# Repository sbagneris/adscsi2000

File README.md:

# ICD AdSCSI 2000 (Advantage 2000) - hardware preservation

The ICD AdSCSI 2000 (silkscreen "ADVANTAGE 2000", 1990) is a Zorro II SCSI controller for the Amiga 2000. Its
three GAL16V8 chips are read-protected and, like many programmable logic parts of that era, are reaching the end
of their data retention. This repository preserves the card: what each GAL does, the complete circuit, and the
measurements behind both, so the card can be repaired, understood and rebuilt.

## What is here

| Path | Contents |
|---|---|
| `docs/hardware.md` | How the card works: Autoconfig, address map, registers, what each GAL does, jumpers, connectors |
| `gals/u3`, `gals/u4`, `gals/u5` | Per-GAL characterisation data and the recovered logic (see below) |
| `gals/uN/uN_named.pld` / `.jed` | GALasm source with board signal names, and the JEDEC file to program a replacement |
| `docs/gal-replacements.md` | Replacement GALs programmed from these files, checked against the originals on the bench and in a real Amiga |
| `schematic/kicad/` | KiCad 10 project: root sheet + 6 sheets, project symbol and footprint libraries, `adscsi2000.pdf`, and the clone PCB (`adscsi2000.kicad_pcb`) |
| `schematic/kicad/fab/` | Ready-to-order clone PCB: gerbers + drill files (`adscsi2000_gerbers.zip`), BOM, previews, `ORDER_NOTES.txt` |
| `schematic/netlist/merged.csv` | The measured netlist: 116 nets, 518 pins |
| `schematic/continuity/` | The raw continuity sweeps the netlist was built from |
| `schematic/tools/` | Photo registration, netlist merging, the netlist-to-KiCad schematic generator and the PCB pipeline |
| `inputs/closeups*/`, `inputs/mycard_*` | Photos of the measured card (both sides, close-up tiles, GAL footprints without sockets) |

## How the GALs were recovered

The originals are secured, so their fuse maps cannot be read. Each chip was characterised in a DuPAL V3
("dupico") board, read-only:

1. A first look classified pins (inputs, driven outputs, tri-stated outputs) and a second read in a different
   input order showed that all three GALs hold state (latches built from output feedback; U4 also uses registers).
2. Each chip's behaviour was mapped exhaustively one input change at a time (and one clock pulse at a time for the
   registered U4): every reachable state and every move from it (`gals/uN/uN_moves*.tsv`), with replays and
   re-clocking to rule out measurement errors.
3. Equations were fitted with espresso and refined until every recorded move (U3 79,824, U4 70,880, U5 12,080)
   replays exactly with outputs allowed to settle in any order (`gals/uN/uN_fit.txt`).
4. GALasm sources were generated and the resulting fuse maps were replayed against the recordings again.

These are **equivalent** equations: they reproduce everything the original can do in circuit, but the secured
originals' exact product terms are unknowable. Combinations the circuit can never reach were don't-cares.

The tools are in the companion repository
[gal-dupico-re](https://github.com/sbagneris/gal-dupico-re).

**Verified on real chips.** ATF16V8B copies programmed from these JEDEC files replay every recorded move of the
originals with no mismatch, and run the card in an Amiga 2000 exactly like the originals: same boots, same quirks,
on both a 68000 and a 68030. See `docs/gal-replacements.md`.

## The clone PCB

A 1:1 through-hole clone of the card, made to validate this work in a real Amiga 2000:

- **Same parts, same places.** Every footprint was fitted to the pin positions measured on the original (scan
  calibrated so all 41 parts land on the original's 0.025" grid), with the outline, mounting holes and finger tab from
  caliper measurements and the Zorro mechanical spec (finger tab 129.26 mm).
- **Same circuit.** The PCB is generated from the measured netlist; KiCad's schematic-parity check is clean.
- **Better ground than the original.** The original has no ground pour; the clone has GND pours on both layers tied
  together by a stitching-via grid every 5 mm, which should help on noisy Zorro buses (68040 accelerators are known to
  trouble the original).
- Two layers, 1.6 mm, signals autorouted (Freerouting) and checked: DRC clean, every documented exception listed in
  `schematic/kicad/drc_accepted.tsv` with its reason.

To order: upload `schematic/kicad/fab/adscsi2000_gerbers.zip` and follow `ORDER_NOTES.txt` (gold fingers with a
bevelled edge). Component values are in the BOM (`adscsi2000_bom.csv`). The three GALs are programmed from
`gals/uN/uN_named.jed` (security fuse off); the boot ROM is not included (see below).

The whole board is reproducible from the scripts in `schematic/tools/`: `pcb_route.sh` (generate + autoroute) then
`pcb_finish.sh` (pours, ground stitching, hand edits replayed, labels, DRC exclusions) and `pcb_fab.sh` (fab outputs).

**Status: not yet built or tested.** The first boards are the test of everything in this repository.

## Status

- GAL logic recovered and named; replacement ATF16V8B chips programmed from the JEDEC files verified on the bench
  (every recorded move of the originals) and in the card (drop-in: same behaviour as the originals).
- Netlist complete and confirmed by continuity on a real card; KiCad schematic generated from it: the exported
  netlist matches the measurements on all 116 nets, ERC clean.
- Clone PCB designed and ready to order (above); next: build and test it, then a compact SMD version.

## Not included

The boot ROM image and ICD's software are copyrighted by ICD Inc. and are not distributed here. Neither are the
third-party reference photos used early on.

## Licences

- Hardware design (`schematic/kicad/`: schematic, PCB, footprints and fabrication files): CERN-OHL-S-2.0
- Software (`schematic/tools/`, scripts): BSD-3-Clause
- Documentation, measurement data, recovered GAL equations and JEDEC files, photos: CC BY-SA 4.0

See `LICENSE.md` and `LICENSES/`. "ICD", "AdSCSI" and "Advantage 2000" are names of their respective owners; this
is an independent preservation project.

## Credits

Measurements, photos and bench work: Stephane Bagneris. Analysis and tooling written with Claude (Anthropic).
DuPAL by the [DuPAL-PAL-DUmper](https://github.com/DuPAL-PAL-DUmper) project. Zorro II pinout from the Amiga
Hardware Reference Manual; 5380 pinout from the NCR 5380 SCSI Interface Chip Design Manual.

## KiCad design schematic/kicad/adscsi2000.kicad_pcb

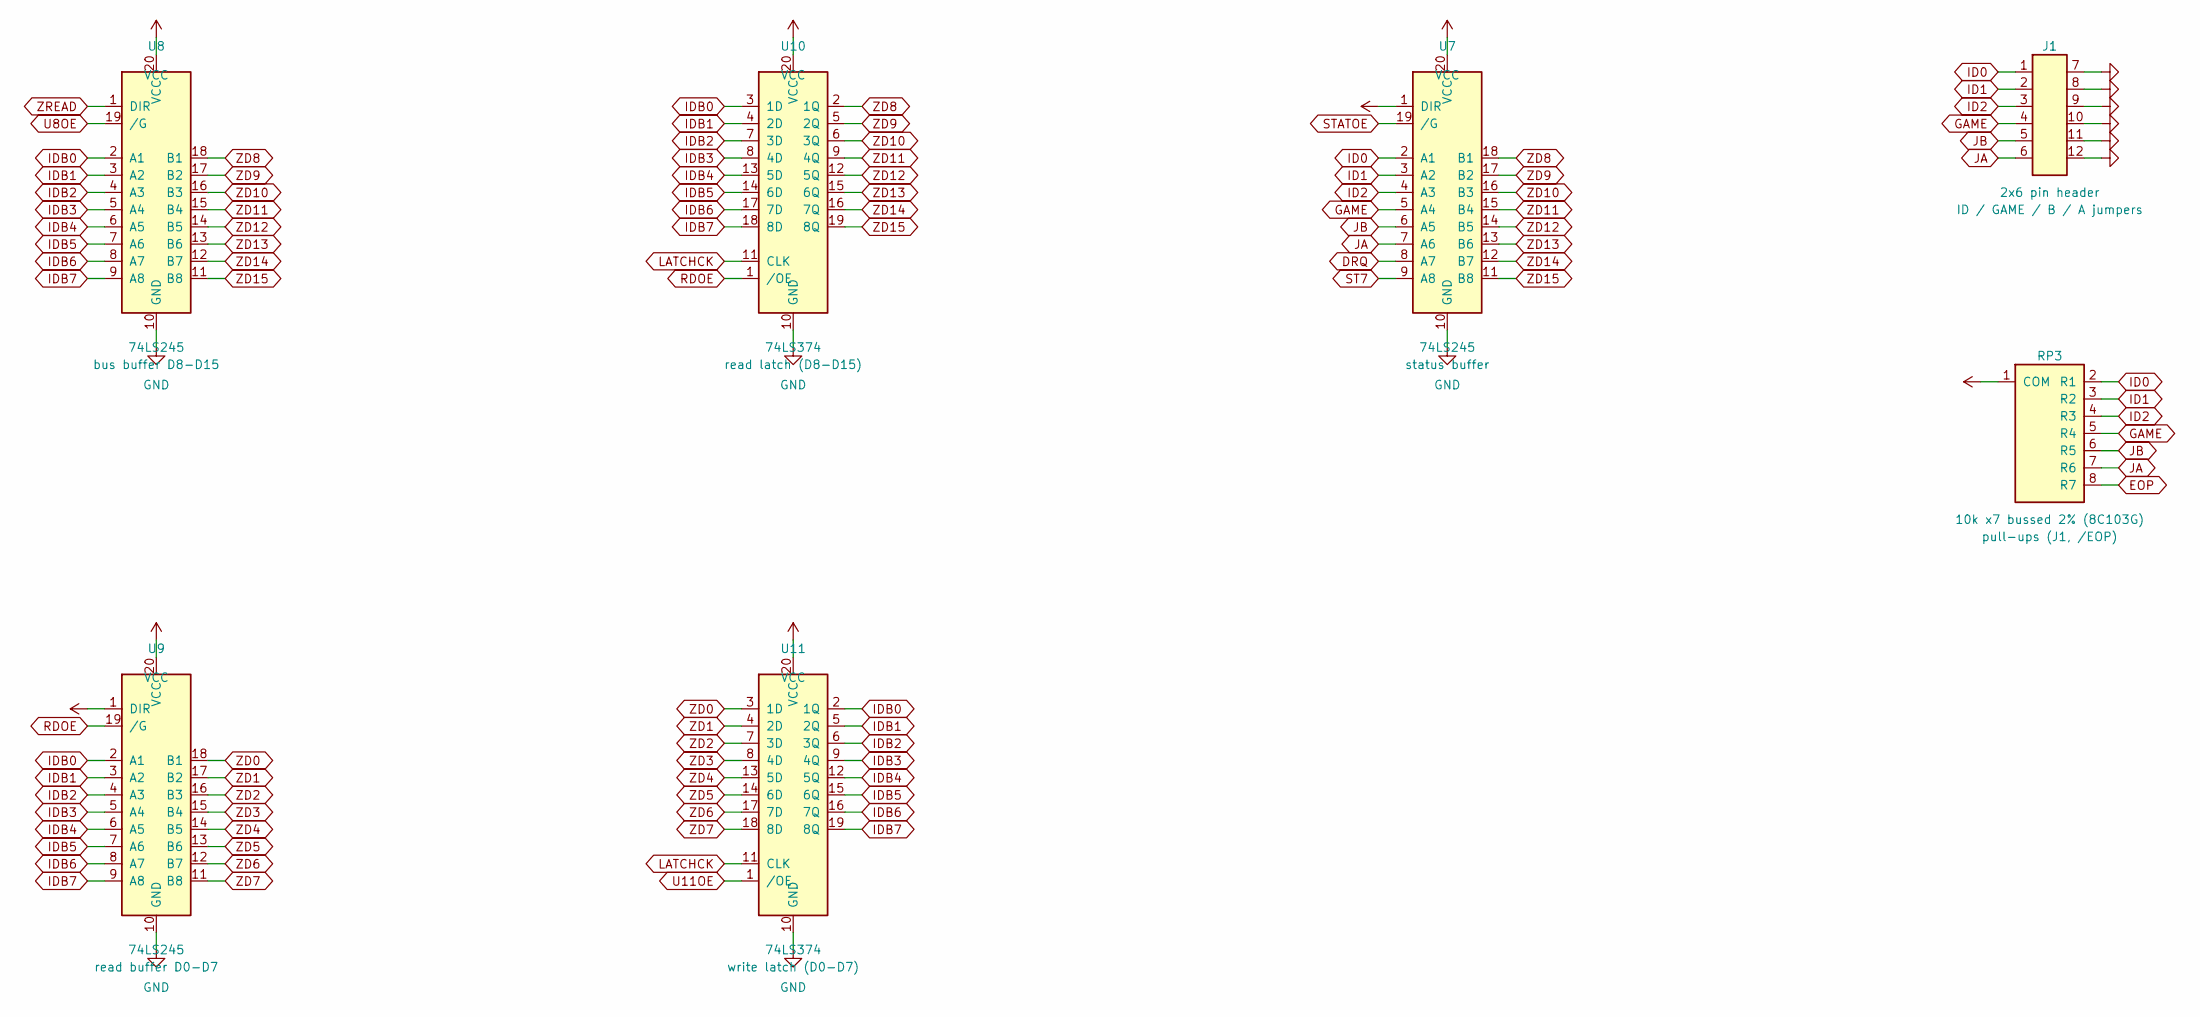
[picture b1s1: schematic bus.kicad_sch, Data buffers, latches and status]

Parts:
J1: 2x6 pin header; PinHeader_2x06_P2.54mm_ColNumbered
RP3: 10k x7 bussed 2% (8C103G); SIP-8_P2.54mm
U7, U8, U9: 74LS245; DIP-20_W7.62mm
U10, U11: 74LS374; DIP-20_W7.62mm

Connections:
DRQ: U7.8 (A7); also elsewhere on the board
EOP: RP3.8 (R7); also elsewhere on the board
GAME: J1.4, RP3.5 (R4), U7.5 (A4); also elsewhere on the board
GND: J1.7, J1.8, J1.9, J1.10, J1.11, J1.12, U7.10 (GND), U8.10 (GND), U9.10 (GND), U10.10 (GND), U11.10 (GND); also elsewhere on the board
ID0: J1.1, RP3.2 (R1), U7.2 (A1)
ID1: J1.2, RP3.3 (R2), U7.3 (A2)
ID2: J1.3, RP3.4 (R3), U7.4 (A3)
IDB0: U8.2 (A1), U9.2 (A1), U10.3 (1D), U11.2 (1Q); also elsewhere on the board
IDB1: U8.3 (A2), U9.3 (A2), U10.4 (2D), U11.5 (2Q); also elsewhere on the board
IDB2: U8.4 (A3), U9.4 (A3), U10.7 (3D), U11.6 (3Q); also elsewhere on the board
IDB3: U8.5 (A4), U9.5 (A4), U10.8 (4D), U11.9 (4Q); also elsewhere on the board
IDB4: U8.6 (A5), U9.6 (A5), U10.13 (5D), U11.12 (5Q); also elsewhere on the board
IDB5: U8.7 (A6), U9.7 (A6), U10.14 (6D), U11.15 (6Q); also elsewhere on the board
IDB6: U8.8 (A7), U9.8 (A7), U10.17 (7D), U11.16 (7Q); also elsewhere on the board
IDB7: U8.9 (A8), U9.9 (A8), U10.18 (8D), U11.19 (8Q); also elsewhere on the board
JA: J1.6, RP3.7 (R6), U7.7 (A6)
JB: J1.5, RP3.6 (R5), U7.6 (A5)
LATCHCK: U10.11 (CLK), U11.11 (CLK); also elsewhere on the board
RDOE: U9.19 (/G), U10.1 (/OE); also elsewhere on the board
ST7: U7.9 (A8); also elsewhere on the board
STATOE: U7.19 (/G); also elsewhere on the board
U8OE: U8.19 (/G); also elsewhere on the board
U11OE: U11.1 (/OE); also elsewhere on the board
VCC: RP3.1 (COM), U7.1 (DIR), U7.20 (VCC), U8.20 (VCC), U9.1 (DIR), U9.20 (VCC), U10.20 (VCC), U11.20 (VCC); also elsewhere on the board
ZD0: U9.18 (B1), U11.3 (1D); also elsewhere on the board
ZD1: U9.17 (B2), U11.4 (2D); also elsewhere on the board
ZD2: U9.16 (B3), U11.7 (3D); also elsewhere on the board
ZD3: U9.15 (B4), U11.8 (4D); also elsewhere on the board
ZD4: U9.14 (B5), U11.13 (5D); also elsewhere on the board
ZD5: U9.13 (B6), U11.14 (6D); also elsewhere on the board
ZD6: U9.12 (B7), U11.17 (7D); also elsewhere on the board
ZD7: U9.11 (B8), U11.18 (8D); also elsewhere on the board
ZD8: U7.18 (B1), U8.18 (B1), U10.2 (1Q); also elsewhere on the board
ZD9: U7.17 (B2), U8.17 (B2), U10.5 (2Q); also elsewhere on the board
ZD10: U7.16 (B3), U8.16 (B3), U10.6 (3Q); also elsewhere on the board
ZD11: U7.15 (B4), U8.15 (B4), U10.9 (4Q); also elsewhere on the board
ZD12: U7.14 (B5), U8.14 (B5), U10.12 (5Q); also elsewhere on the board
ZD13: U7.13 (B6), U8.13 (B6), U10.15 (6Q); also elsewhere on the board
ZD14: U7.12 (B7), U8.12 (B7), U10.16 (7Q); also elsewhere on the board
ZD15: U7.11 (B8), U8.11 (B8), U10.19 (8Q); also elsewhere on the board
ZREAD: U8.1 (DIR); also elsewhere on the board

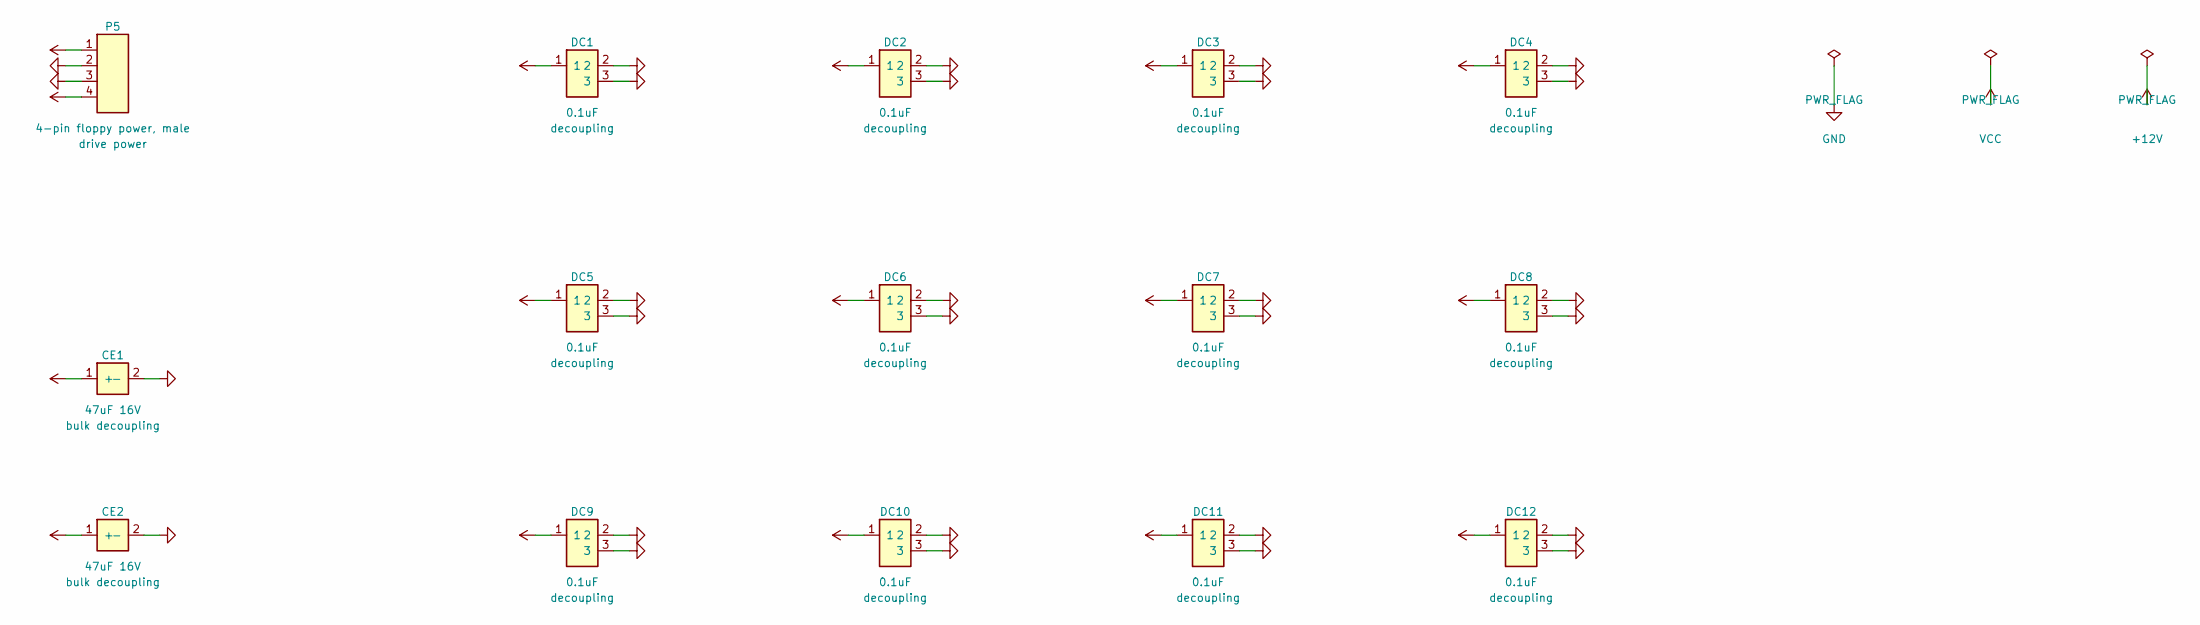
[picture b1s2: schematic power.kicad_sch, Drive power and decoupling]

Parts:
CE1, CE2: 47uF 16V; CP_Radial_P2.54_D5.0
DC1, DC2, DC3, DC4, DC5, DC6, DC7, DC8, DC9, DC10, DC11, DC12: 0.1uF; C_Disc_3pad_P2.54_P10.16
P5: 4-pin floppy power, male; DrivePower_1x04_P2.54mm

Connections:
+12V: P5.1; also elsewhere on the board
GND: CE1.2 (-), CE2.2 (-), DC1.2, DC1.3, DC2.2, DC2.3, DC3.2, DC3.3, DC4.2, DC4.3, DC5.2, DC5.3, DC6.2, DC6.3, DC7.2, DC7.3, DC8.2, DC8.3, DC9.2, DC9.3, DC10.2, DC10.3, DC11.2, DC11.3, DC12.2, DC12.3, P5.2, P5.3; also elsewhere on the board
VCC: CE1.1 (+), CE2.1 (+), DC1.1, DC2.1, DC3.1, DC4.1, DC5.1, DC6.1, DC7.1, DC8.1, DC9.1, DC10.1, DC11.1, DC12.1, P5.4; also elsewhere on the board

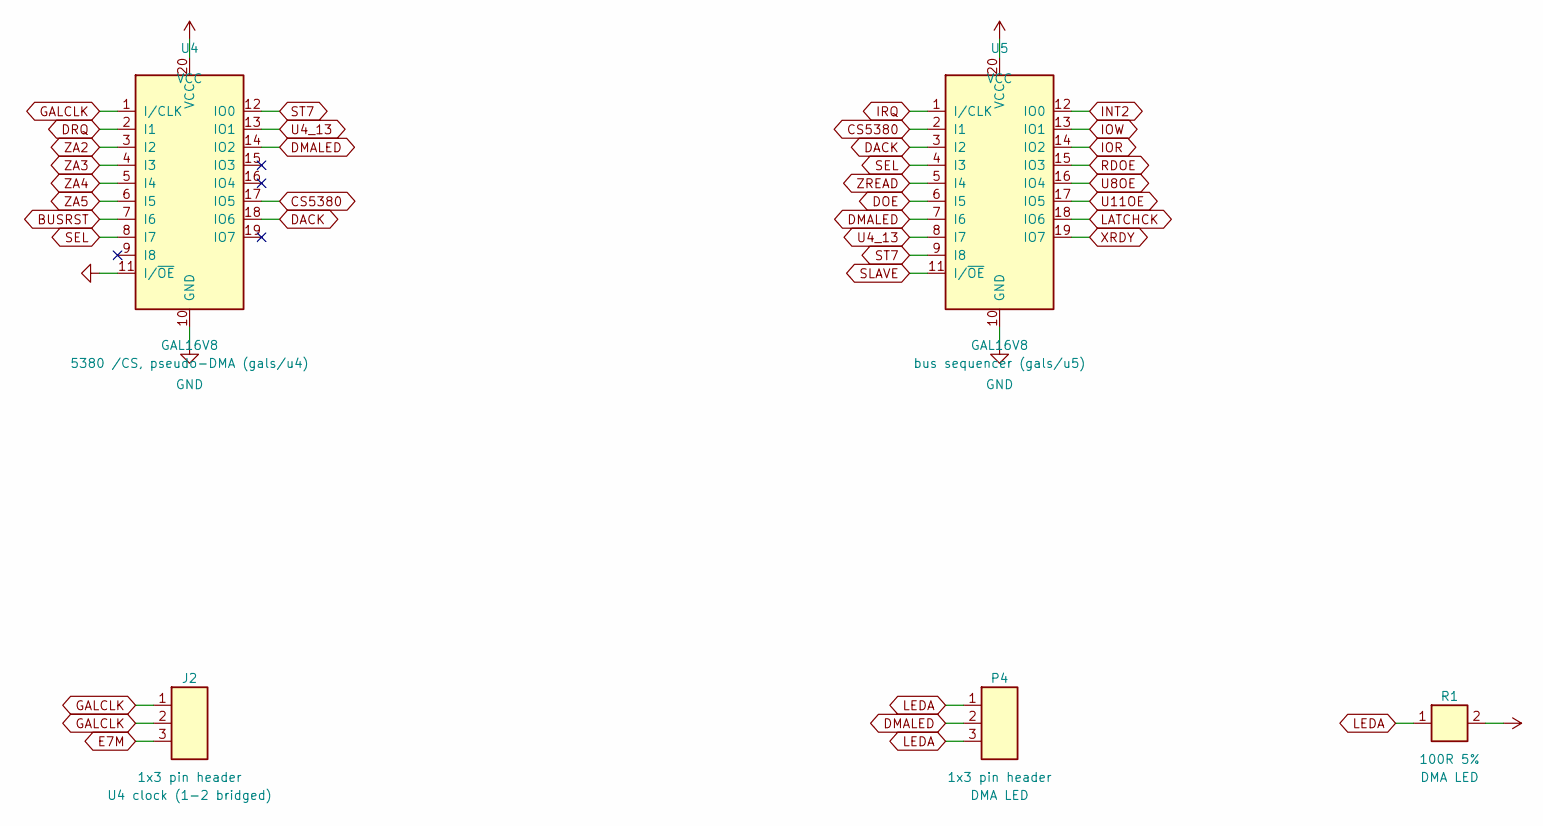
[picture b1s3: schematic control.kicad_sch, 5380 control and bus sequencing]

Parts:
J2: 1x3 pin header; PinHeader_1x03_P2.54mm
P4: 1x3 pin header; PinHeader_1x03_P2.54mm
R1: 100R 5%; Axial_P10.16mm
U4, U5: GAL16V8; DIP-20_W7.62mm_Socket

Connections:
BUSRST: U4.7 (I6); also elsewhere on the board
CS5380: U4.17 (IO5), U5.2 (I1); also elsewhere on the board
DACK: U4.18 (IO6), U5.3 (I2); also elsewhere on the board
DMALED: P4.2, U4.14 (IO2), U5.7 (I6)
DOE: U5.6 (I5); also elsewhere on the board
DRQ: U4.2 (I1); also elsewhere on the board
E7M: J2.3; also elsewhere on the board
GALCLK: J2.1, J2.2, U4.1 (I/CLK); also elsewhere on the board
GND: U4.10 (GND), U4.11 (I/~OE), U5.10 (GND); also elsewhere on the board
INT2: U5.12 (IO0); also elsewhere on the board
IOR: U5.14 (IO2); also elsewhere on the board
IOW: U5.13 (IO1); also elsewhere on the board
IRQ: U5.1 (I/CLK); also elsewhere on the board
LATCHCK: U5.18 (IO6); also elsewhere on the board
LEDA: P4.1, P4.3, R1.1
RDOE: U5.15 (IO3); also elsewhere on the board
SEL: U4.8 (I7), U5.4 (I3); also elsewhere on the board
SLAVE: U5.11 (I/~OE); also elsewhere on the board
ST7: U4.12 (IO0), U5.9 (I8); also elsewhere on the board
U4_13: U4.13 (IO1), U5.8 (I7)
U8OE: U5.16 (IO4); also elsewhere on the board
U11OE: U5.17 (IO5); also elsewhere on the board
VCC: R1.2, U4.20 (VCC), U5.20 (VCC); also elsewhere on the board
XRDY: U5.19 (IO7); also elsewhere on the board
ZA2: U4.3 (I2); also elsewhere on the board
ZA3: U4.4 (I3); also elsewhere on the board
ZA4: U4.5 (I4); also elsewhere on the board
ZA5: U4.6 (I5); also elsewhere on the board
ZREAD: U5.5 (I4); also elsewhere on the board

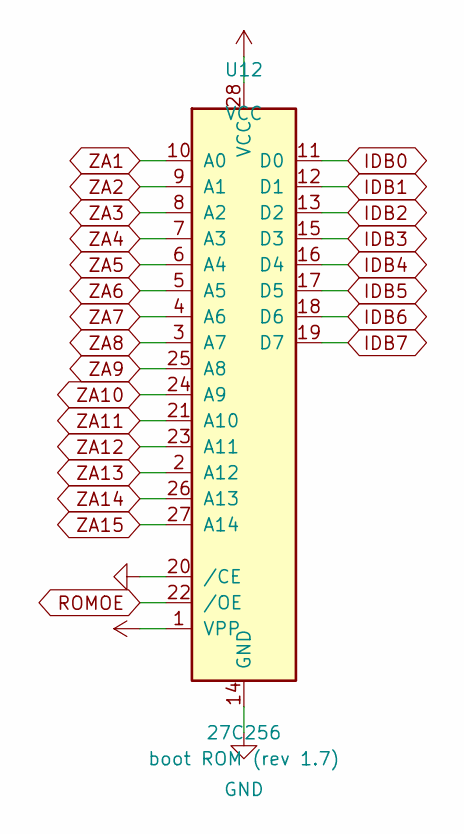
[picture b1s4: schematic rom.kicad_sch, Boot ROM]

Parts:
U12: 27C256; DIP-28_W15.24mm_Socket

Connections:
GND: U12.14 (GND), U12.20 (/CE); also elsewhere on the board
IDB0: U12.11 (D0); also elsewhere on the board
IDB1: U12.12 (D1); also elsewhere on the board
IDB2: U12.13 (D2); also elsewhere on the board
IDB3: U12.15 (D3); also elsewhere on the board
IDB4: U12.16 (D4); also elsewhere on the board
IDB5: U12.17 (D5); also elsewhere on the board
IDB6: U12.18 (D6); also elsewhere on the board
IDB7: U12.19 (D7); also elsewhere on the board
ROMOE: U12.22 (/OE); also elsewhere on the board
VCC: U12.1 (VPP), U12.28 (VCC); also elsewhere on the board
ZA1: U12.10 (A0); also elsewhere on the board
ZA2: U12.9 (A1); also elsewhere on the board
ZA3: U12.8 (A2); also elsewhere on the board
ZA4: U12.7 (A3); also elsewhere on the board
ZA5: U12.6 (A4); also elsewhere on the board
ZA6: U12.5 (A5); also elsewhere on the board
ZA7: U12.4 (A6); also elsewhere on the board
ZA8: U12.3 (A7); also elsewhere on the board
ZA9: U12.25 (A8); also elsewhere on the board
ZA10: U12.24 (A9); also elsewhere on the board
ZA11: U12.21 (A10); also elsewhere on the board
ZA12: U12.23 (A11); also elsewhere on the board
ZA13: U12.2 (A12); also elsewhere on the board
ZA14: U12.26 (A13); also elsewhere on the board
ZA15: U12.27 (A14); also elsewhere on the board

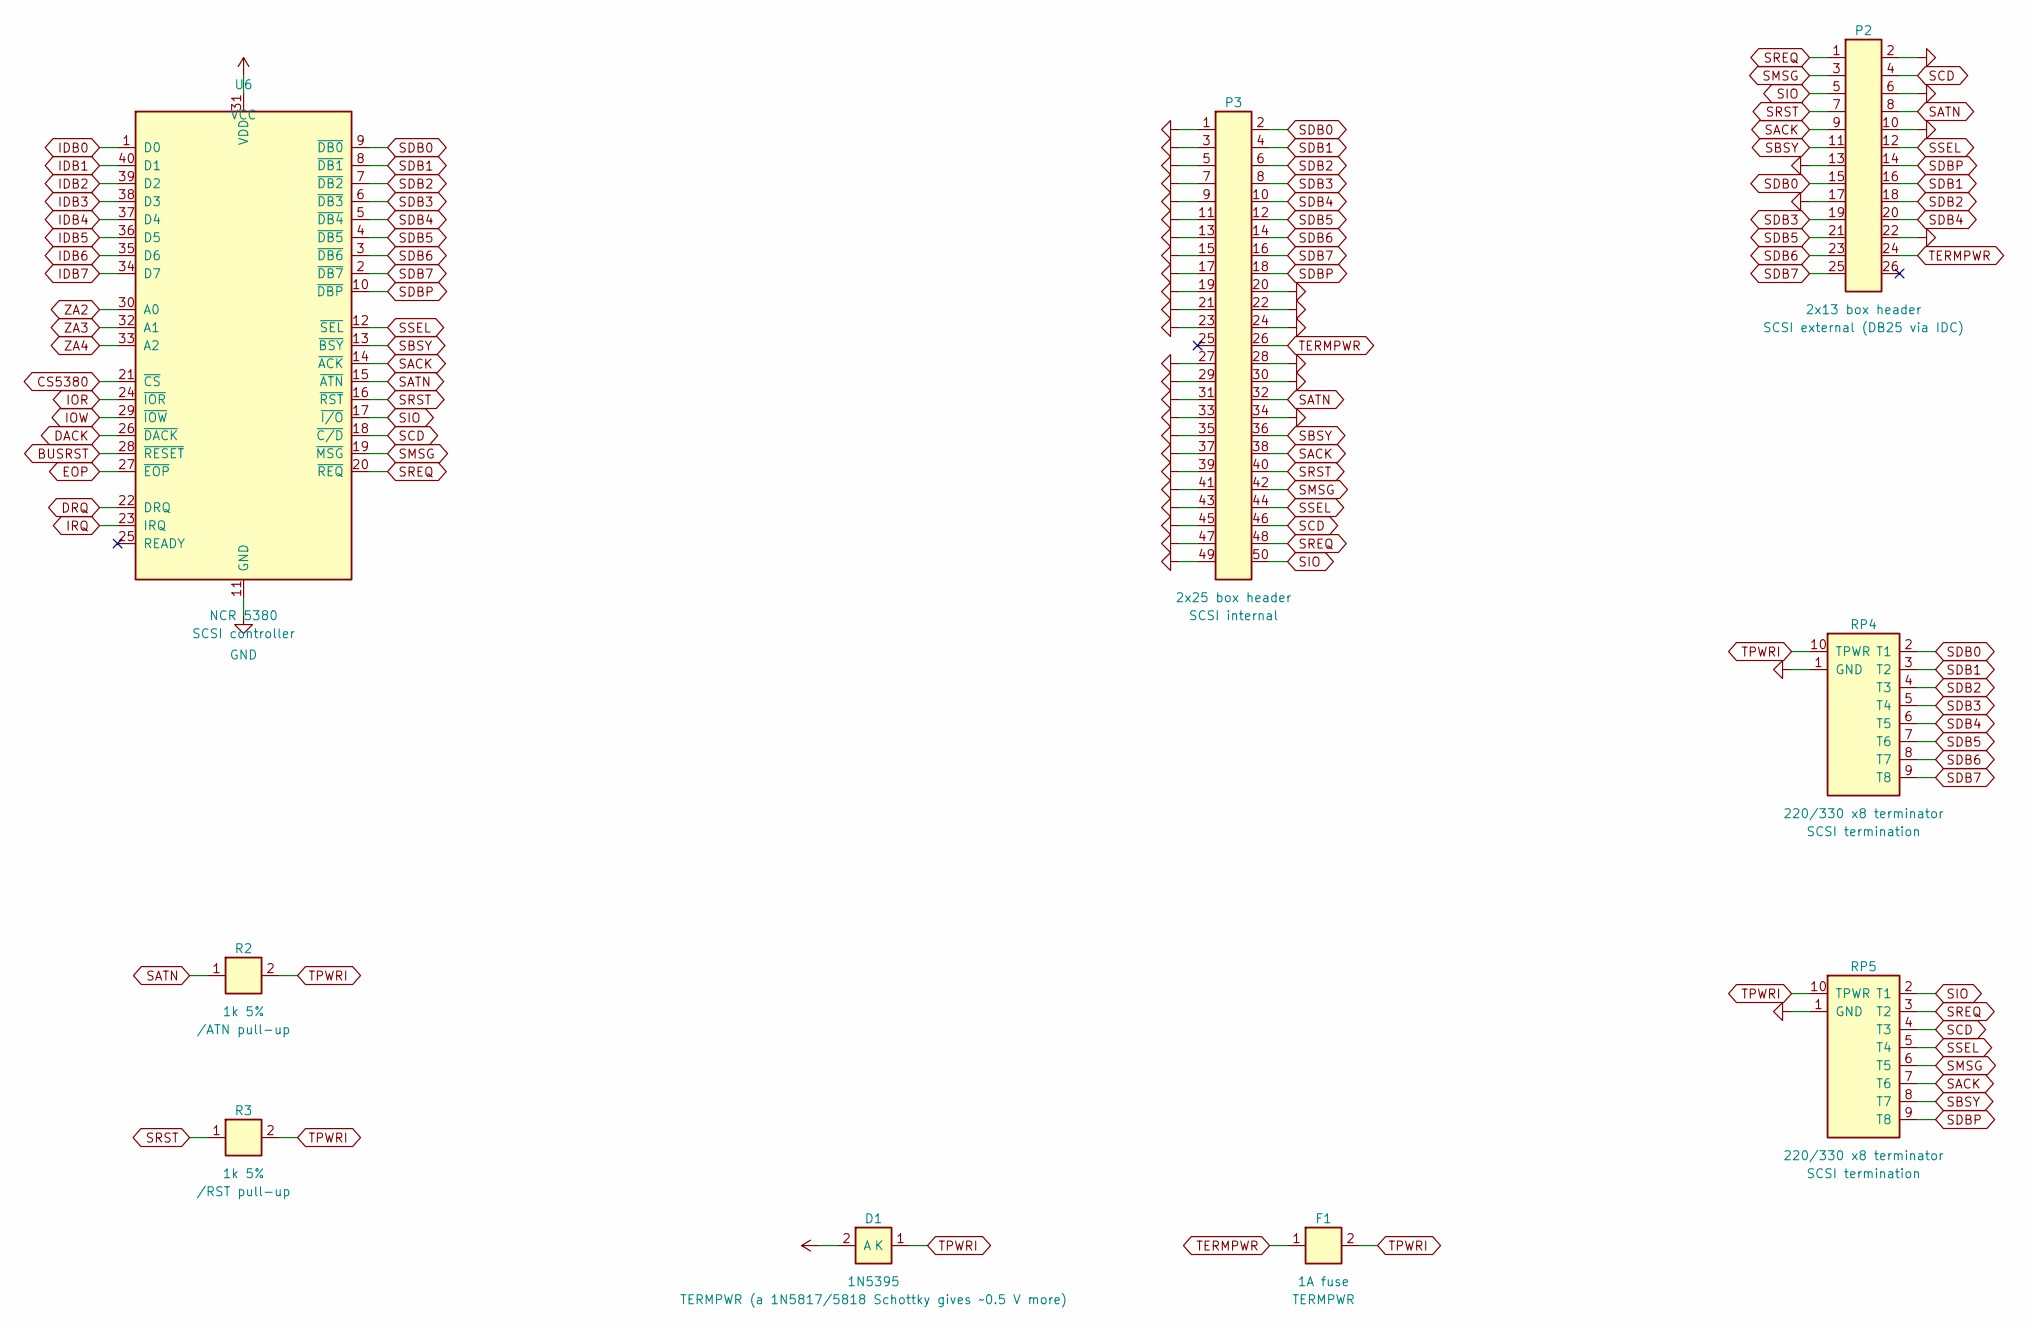
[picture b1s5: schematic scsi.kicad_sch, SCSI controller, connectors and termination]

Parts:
D1: 1N5395; Diode_Axial_P10.16mm
F1: 1A fuse; Axial_P10.16mm_D1.0
P2: 2x13 box header; IDC-Box_2x13_P2.54mm
P3: 2x25 box header; IDC-Box_2x25_P2.54mm
R2, R3: 1k 5%; Axial_P10.16mm
RP4, RP5: 220/330 x8 terminator; SIP-10_P2.54mm
U6: NCR 5380; DIP-40_W15.24mm_Socket

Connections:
BUSRST: U6.28 (~RESET); also elsewhere on the board
CS5380: U6.21 (~CS); also elsewhere on the board
DACK: U6.26 (~DACK); also elsewhere on the board
DRQ: U6.22 (DRQ); also elsewhere on the board
EOP: U6.27 (~EOP); also elsewhere on the board
GND: P2.2, P2.6, P2.10, P2.13, P2.17, P2.22, P3.1, P3.3, P3.5, P3.7, P3.9, P3.11, P3.13, P3.15, P3.17, P3.19, P3.20, P3.21, P3.22, P3.23, P3.24, P3.27, P3.28, P3.29, P3.30, P3.31, P3.33, P3.34, P3.35, P3.37, P3.39, P3.41, P3.43, P3.45, P3.47, P3.49, RP4.1 (GND), RP5.1 (GND), U6.11 (GND); also elsewhere on the board
IDB0: U6.1 (D0); also elsewhere on the board
IDB1: U6.40 (D1); also elsewhere on the board
IDB2: U6.39 (D2); also elsewhere on the board
IDB3: U6.38 (D3); also elsewhere on the board
IDB4: U6.37 (D4); also elsewhere on the board
IDB5: U6.36 (D5); also elsewhere on the board
IDB6: U6.35 (D6); also elsewhere on the board
IDB7: U6.34 (D7); also elsewhere on the board
IOR: U6.24 (~IOR); also elsewhere on the board
IOW: U6.29 (~IOW); also elsewhere on the board
IRQ: U6.23 (IRQ); also elsewhere on the board
SACK: P2.9, P3.38, RP5.7 (T6), U6.14 (~ACK)
SATN: P2.8, P3.32, R2.1, U6.15 (~ATN)
SBSY: P2.11, P3.36, RP5.8 (T7), U6.13 (~BSY)
SCD: P2.4, P3.46, RP5.4 (T3), U6.18 (~C/D)
SDB0: P2.15, P3.2, RP4.2 (T1), U6.9 (~DB0)
SDB1: P2.16, P3.4, RP4.3 (T2), U6.8 (~DB1)
SDB2: P2.18, P3.6, RP4.4 (T3), U6.7 (~DB2)
SDB3: P2.19, P3.8, RP4.5 (T4), U6.6 (~DB3)
SDB4: P2.20, P3.10, RP4.6 (T5), U6.5 (~DB4)
SDB5: P2.21, P3.12, RP4.7 (T6), U6.4 (~DB5)
SDB6: P2.23, P3.14, RP4.8 (T7), U6.3 (~DB6)
SDB7: P2.25, P3.16, RP4.9 (T8), U6.2 (~DB7)
SDBP: P2.14, P3.18, RP5.9 (T8), U6.10 (~DBP)
SIO: P2.5, P3.50, RP5.2 (T1), U6.17 (~I/O)
SMSG: P2.3, P3.42, RP5.6 (T5), U6.19 (~MSG)
SREQ: P2.1, P3.48, RP5.3 (T2), U6.20 (~REQ)
SRST: P2.7, P3.40, R3.1, U6.16 (~RST)
SSEL: P2.12, P3.44, RP5.5 (T4), U6.12 (~SEL)
TERMPWR: F1.1, P2.24, P3.26
TPWRI: D1.1 (K), F1.2, R2.2, R3.2, RP4.10 (TPWR), RP5.10 (TPWR)
VCC: D1.2 (A), U6.31 (VDD); also elsewhere on the board
ZA2: U6.30 (A0); also elsewhere on the board
ZA3: U6.32 (A1); also elsewhere on the board
ZA4: U6.33 (A2); also elsewhere on the board

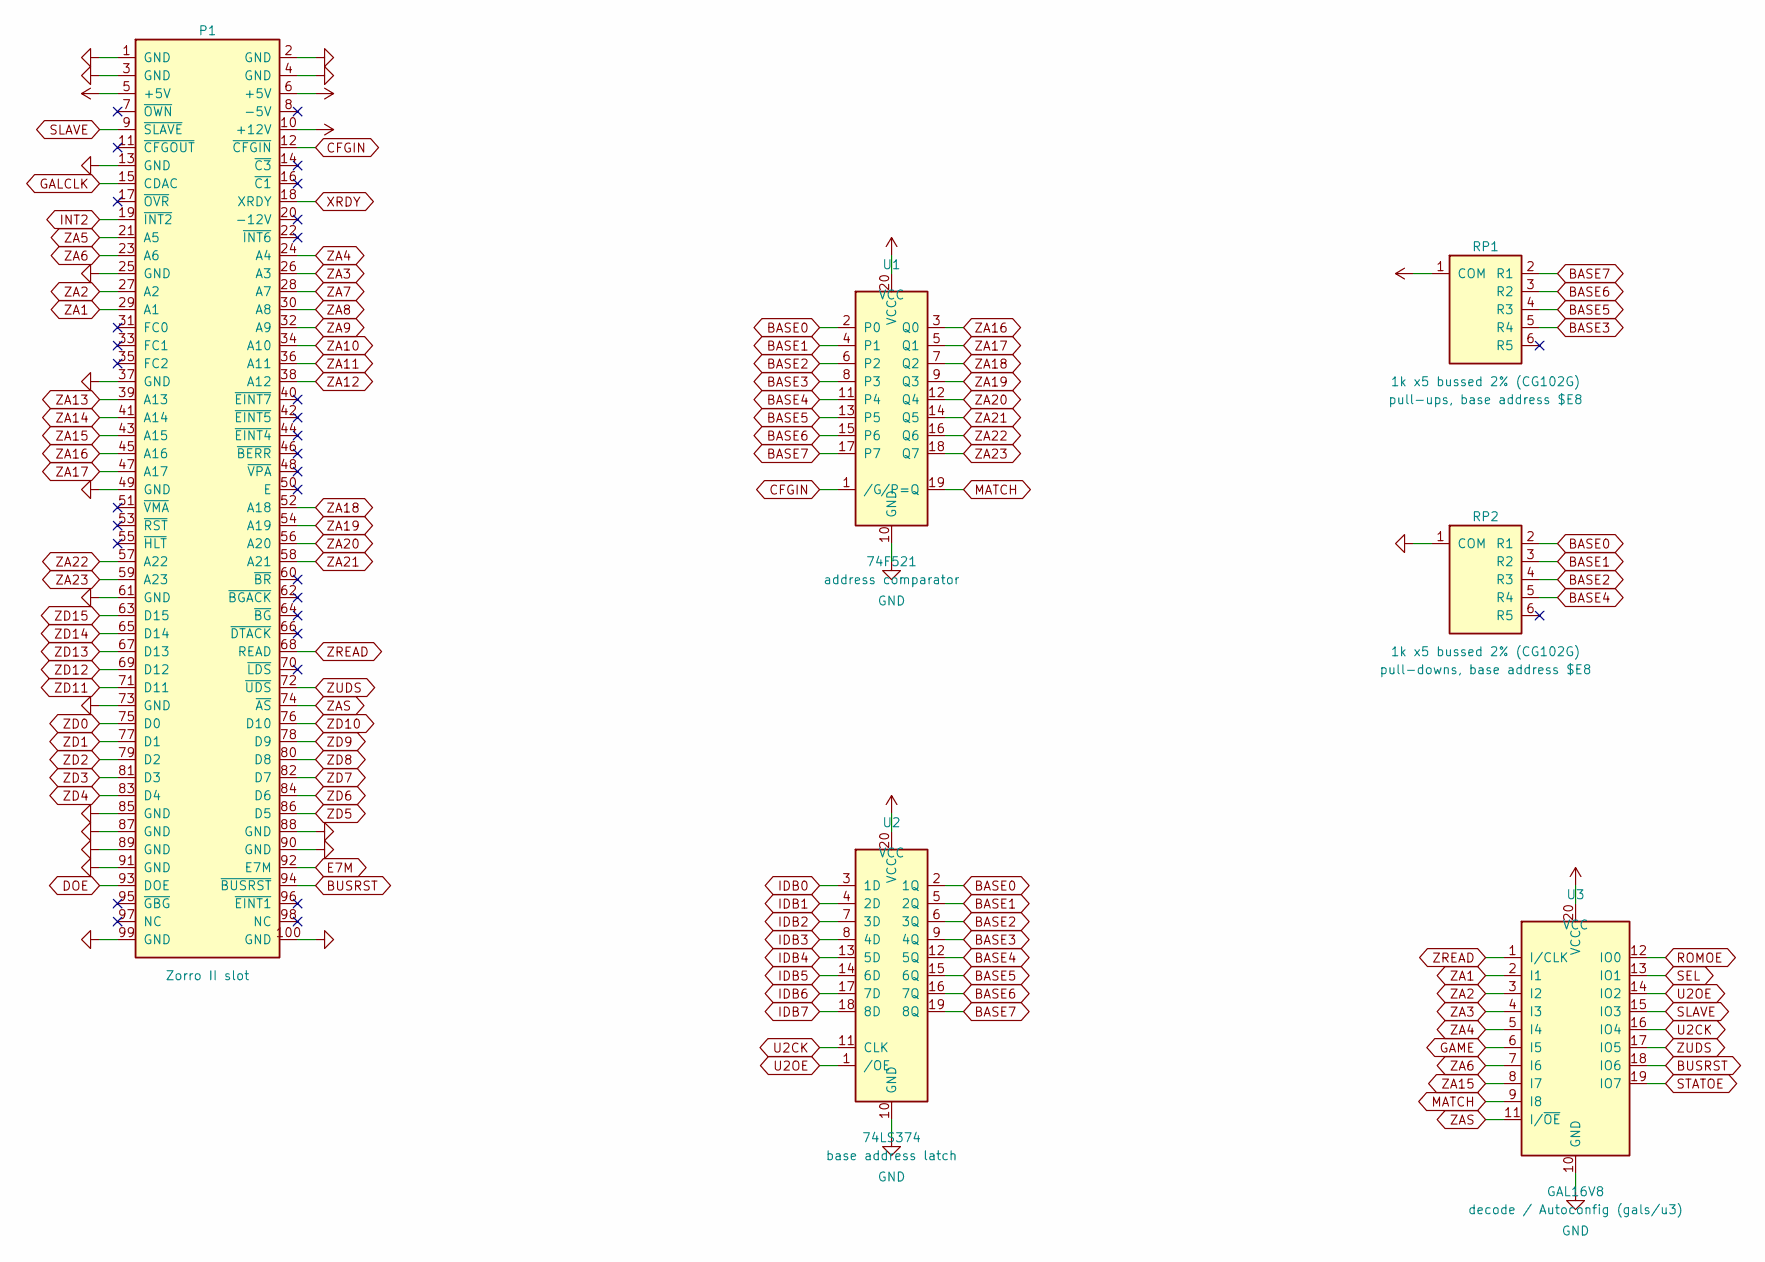
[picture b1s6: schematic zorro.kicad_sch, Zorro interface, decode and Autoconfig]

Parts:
P1: Zorro II slot; Zorro2_Edge_100
RP1, RP2: 1k x5 bussed 2% (CG102G); SIP-6_P2.54mm
U1: 74F521; DIP-20_W7.62mm
U2: 74LS374; DIP-20_W7.62mm
U3: GAL16V8; DIP-20_W7.62mm_Socket

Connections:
+12V: P1.10 (+12V); also elsewhere on the board
BASE0: RP2.2 (R1), U1.2 (P0), U2.2 (1Q)
BASE1: RP2.3 (R2), U1.4 (P1), U2.5 (2Q)
BASE2: RP2.4 (R3), U1.6 (P2), U2.6 (3Q)
BASE3: RP1.5 (R4), U1.8 (P3), U2.9 (4Q)
BASE4: RP2.5 (R4), U1.11 (P4), U2.12 (5Q)
BASE5: RP1.4 (R3), U1.13 (P5), U2.15 (6Q)
BASE6: RP1.3 (R2), U1.15 (P6), U2.16 (7Q)
BASE7: RP1.2 (R1), U1.17 (P7), U2.19 (8Q)
BUSRST: P1.94 (~BUSRST), U3.18 (IO6); also elsewhere on the board
CFGIN: P1.12 (~CFGIN), U1.1 (/G)
DOE: P1.93 (DOE); also elsewhere on the board
E7M: P1.92 (E7M); also elsewhere on the board
GALCLK: P1.15 (CDAC); also elsewhere on the board
GAME: U3.6 (I5); also elsewhere on the board
GND: P1.1 (GND), P1.2 (GND), P1.3 (GND), P1.4 (GND), P1.13 (GND), P1.25 (GND), P1.37 (GND), P1.49 (GND), P1.61 (GND), P1.73 (GND), P1.85 (GND), P1.87 (GND), P1.88 (GND), P1.89 (GND), P1.90 (GND), P1.91 (GND), P1.99 (GND), P1.100 (GND), RP2.1 (COM), U1.10 (GND), U2.10 (GND), U3.10 (GND); also elsewhere on the board
IDB0: U2.3 (1D); also elsewhere on the board
IDB1: U2.4 (2D); also elsewhere on the board
IDB2: U2.7 (3D); also elsewhere on the board
IDB3: U2.8 (4D); also elsewhere on the board
IDB4: U2.13 (5D); also elsewhere on the board
IDB5: U2.14 (6D); also elsewhere on the board
IDB6: U2.17 (7D); also elsewhere on the board
IDB7: U2.18 (8D); also elsewhere on the board
INT2: P1.19 (~INT2); also elsewhere on the board
MATCH: U1.19 (/P=Q), U3.9 (I8)
ROMOE: U3.12 (IO0); also elsewhere on the board
SEL: U3.13 (IO1); also elsewhere on the board
SLAVE: P1.9 (~SLAVE), U3.15 (IO3); also elsewhere on the board
STATOE: U3.19 (IO7); also elsewhere on the board
U2CK: U2.11 (CLK), U3.16 (IO4)
U2OE: U2.1 (/OE), U3.14 (IO2)
VCC: P1.5 (+5V), P1.6 (+5V), RP1.1 (COM), U1.20 (VCC), U2.20 (VCC), U3.20 (VCC); also elsewhere on the board
XRDY: P1.18 (XRDY); also elsewhere on the board
ZA1: P1.29 (A1), U3.2 (I1); also elsewhere on the board
ZA2: P1.27 (A2), U3.3 (I2); also elsewhere on the board
ZA3: P1.26 (A3), U3.4 (I3); also elsewhere on the board
ZA4: P1.24 (A4), U3.5 (I4); also elsewhere on the board
ZA5: P1.21 (A5); also elsewhere on the board
ZA6: P1.23 (A6), U3.7 (I6); also elsewhere on the board
ZA7: P1.28 (A7); also elsewhere on the board
ZA8: P1.30 (A8); also elsewhere on the board
ZA9: P1.32 (A9); also elsewhere on the board
ZA10: P1.34 (A10); also elsewhere on the board
ZA11: P1.36 (A11); also elsewhere on the board
ZA12: P1.38 (A12); also elsewhere on the board
ZA13: P1.39 (A13); also elsewhere on the board
ZA14: P1.41 (A14); also elsewhere on the board
ZA15: P1.43 (A15), U3.8 (I7); also elsewhere on the board
ZA16: P1.45 (A16), U1.3 (Q0)
ZA17: P1.47 (A17), U1.5 (Q1)
ZA18: P1.52 (A18), U1.7 (Q2)
ZA19: P1.54 (A19), U1.9 (Q3)
ZA20: P1.56 (A20), U1.12 (Q4)
ZA21: P1.58 (A21), U1.14 (Q5)
ZA22: P1.57 (A22), U1.16 (Q6)
ZA23: P1.59 (A23), U1.18 (Q7)
ZAS: P1.74 (~AS), U3.11 (I/~OE)
ZD0: P1.75 (D0); also elsewhere on the board
ZD1: P1.77 (D1); also elsewhere on the board
ZD2: P1.79 (D2); also elsewhere on the board
ZD3: P1.81 (D3); also elsewhere on the board
ZD4: P1.83 (D4); also elsewhere on the board
ZD5: P1.86 (D5); also elsewhere on the board
ZD6: P1.84 (D6); also elsewhere on the board
ZD7: P1.82 (D7); also elsewhere on the board
ZD8: P1.80 (D8); also elsewhere on the board
ZD9: P1.78 (D9); also elsewhere on the board
ZD10: P1.76 (D10); also elsewhere on the board
ZD11: P1.71 (D11); also elsewhere on the board
ZD12: P1.69 (D12); also elsewhere on the board
ZD13: P1.67 (D13); also elsewhere on the board
ZD14: P1.65 (D14); also elsewhere on the board
ZD15: P1.63 (D15); also elsewhere on the board
ZREAD: P1.68 (READ), U3.1 (I/CLK); also elsewhere on the board
ZUDS: P1.72 (~UDS), U3.17 (IO5)

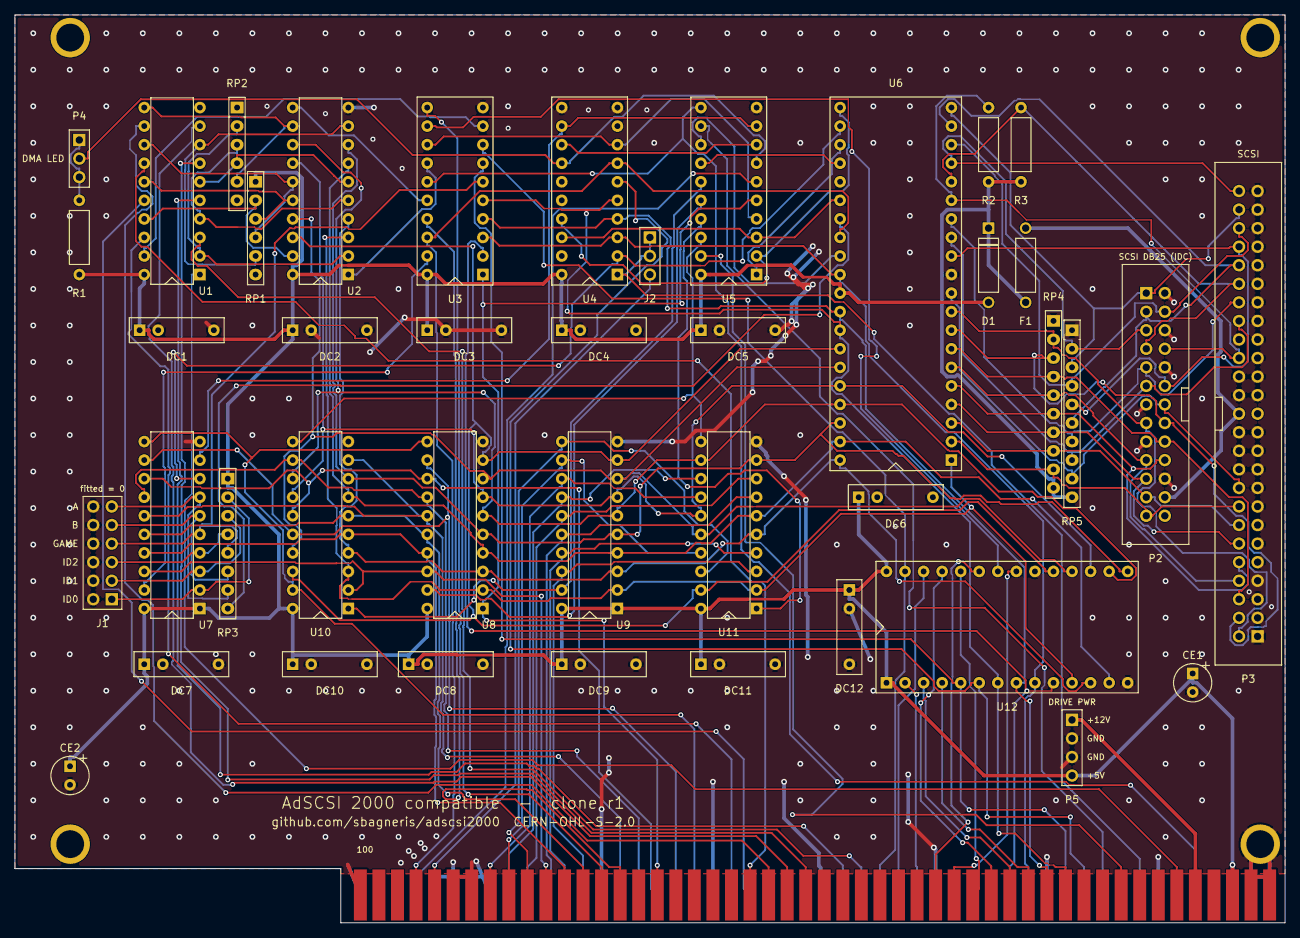
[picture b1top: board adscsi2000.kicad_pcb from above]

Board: 2 copper layers, 173.8 x 124.3 mm, 47 parts (0 on the bottom side), 116 nets.

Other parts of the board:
H1, H2, H3, H4: mounting hole; MountingHole_3.8mm_Pad5.4

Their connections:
GND: H4.1; also elsewhere on the board

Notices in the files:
schematic/kicad/adscsi2000.kicad_pcb:
github.com/sbagneris/adscsi2000  CERN-OHL-S-2.0
